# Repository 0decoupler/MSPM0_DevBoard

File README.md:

# MSPM0 MCU Devboard

some of the problems as of now:
- [ ] SPI, PWM, and GPIO header traces are trash, made the whole layout a spaghetti
- [ ] long via traces through the bottom layer, which is a rael problem
- [ ] some signal lines like PWM and ADC are subject to noise pickup due to closeness to 3V3 and VBUS thick traces.
- [ ] LDO's GND and VBUS copper fill field zones are killing my eyes. seems like abstract art or smth.
- [ ] ... 

3D View:

PCB Layout:

These are subject to change with each commit. Just to keep the repo neat.

⛄️

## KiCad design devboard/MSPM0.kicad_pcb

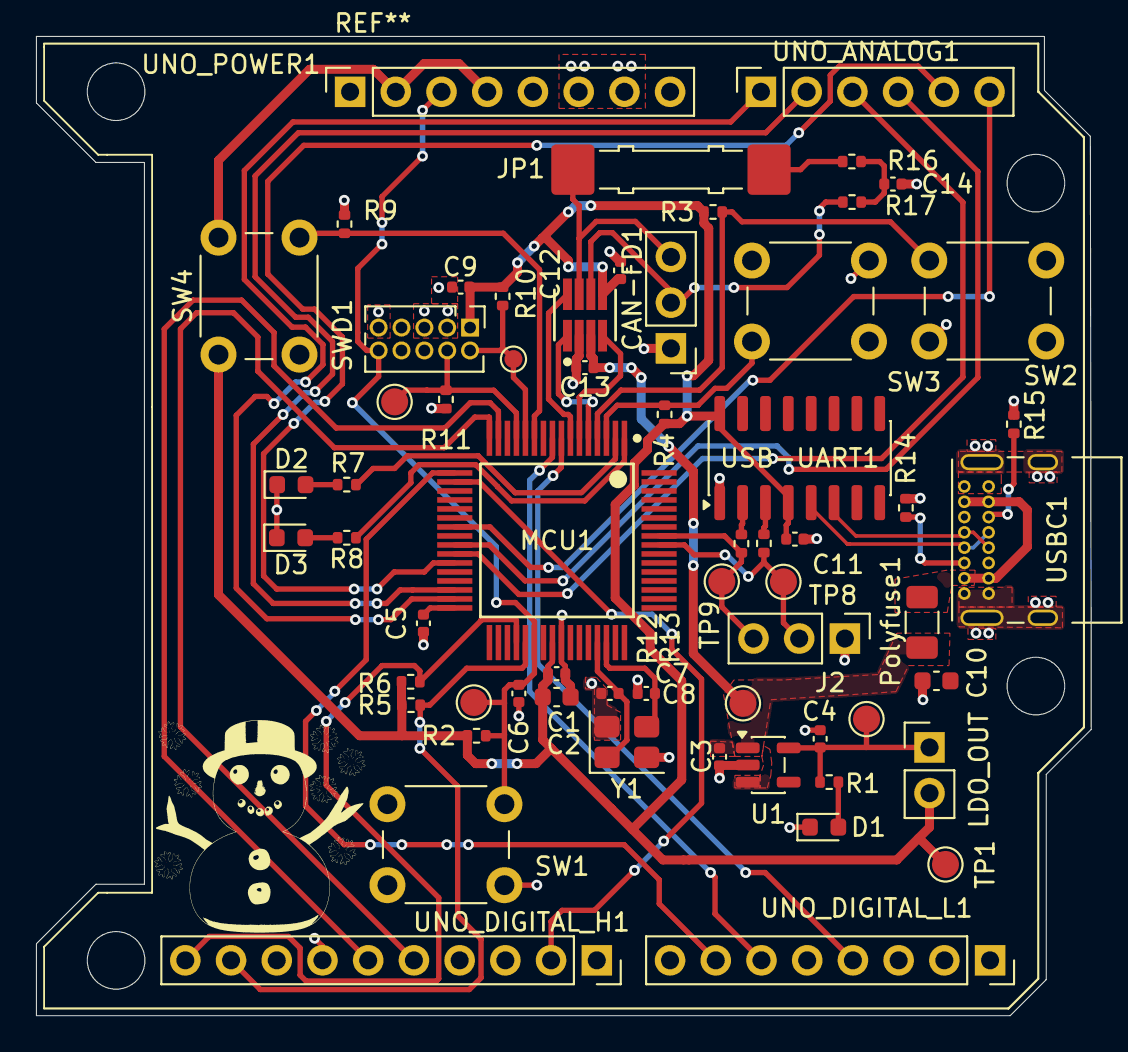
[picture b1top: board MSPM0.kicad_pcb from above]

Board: 2 copper layers, 58.6 x 54.4 mm, 62 parts (0 on the bottom side), 50 nets.

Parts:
C1, C10: 10u; C_0603_1608Metric
C2, C11, C12, C13: 100n; C_0402_1005Metric
C3, C4: 1u; C_0402_1005Metric
C5, C9: 470n; C_0402_1005Metric
C6: 10n; C_0402_1005Metric
C7, C8: 15p; C_0402_1005Metric
C14: 4n7; C_0402_1005Metric
CAN-FD1: TCAN1044AVDDFRQ1.A; DDF0008A-IPC_A
D1: RED; LED_0603_1608Metric
D2: BLUE; LED_0603_1608Metric
D3: GREEN; LED_0603_1608Metric
J2, J3: Conn_01x03_Pin; PinHeader_1x03_P2.54mm_Vertical
JP1: Jumper_2_Bridged; Jumper_Harwin_S1621_P10.9mm
LDO_OUT: Conn_01x02; PinHeader_1x02_P2.54mm_Vertical
MCU1: MSPM0G3507SPMR (LQFP-64); PM0064A-IPC_A
Polyfuse1: 500mA; Fuse_1206_3216Metric
R1: 470R; R_0402_1005Metric
R2, R9: 47k; R_0402_1005Metric
R3, R4, R10, R11: 10k; R_0402_1005Metric
R5, R6: 4k7; R_0402_1005Metric
R7, R8, R12, R13: 1k; R_0402_1005Metric
R14, R15: 5k1; R_0402_1005Metric
R16, R17: 62R; R_0402_1005Metric
SW1: SW_Push; SW_PUSH_6mm
SW2, SW3: SW_Push; SW_PUSH_6mm_H7.3mm
SW4: SW; SW_PUSH_6mm
SWD1: SWD; PinHeader_2x05_P1.27mm_Vertical
TP1, TP3: TP_3V3; TestPoint_Pad_D1.5mm
TP2: TP_5V; TestPoint_Pad_D1.5mm
TP5: TP_NRST; TestPoint_Pad_D1.5mm
TP6: TP_SWDIO; TestPoint_Pad_D1.0mm
TP7: TP_SWDCLK; TestPoint_Pad_D1.5mm
TP8: TP_UART_TX; TestPoint_Pad_D1.5mm
TP9: TP_UART_RX; TestPoint_Pad_D1.5mm
U1: AP2112K-3.3; SOT-23-5
UNO_ANALOG1: Conn_01x06_Analog; PinSocket_1x06_P2.54mm_Vertical
UNO_DIGITAL_H1: Conn_01x10_DigitalHigh; PinSocket_1x10_P2.54mm_Vertical
UNO_DIGITAL_L1: Conn_01x08_DigitalLow; PinSocket_1x08_P2.54mm_Vertical
UNO_POWER1: Conn_01x08_Power; PinSocket_1x08_P2.54mm_Vertical
USB-UART1: CH340C; SOIC-16_3.9x9.9mm_P1.27mm
USBC1: USB_C_Receptacle; USB_C_Receptacle_GCT_USB4085
Y1: 40MHz; Crystal_SMD_3225-4Pin_3.2x2.5mm

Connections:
+3V3: C1.1, C2.1, C9.1, C11.2, C12.1, CAN-FD1.5 (VIO), LDO_OUT.2, MCU1.40 (VDD), R2.1, R3.1, R4.1, R5.1, R6.1, R10.1, SW4.1, SWD1.1 (VTref), TP1.1 (1_1), UNO_POWER1.2, UNO_POWER1.4, USB-UART1.4 (V3), USB-UART1.16 (VCC)
/ADC12_0: MCU1.31 (PA27_A0_0_CAN_RX), UNO_ANALOG1.1
/ADC12_1: MCU1.30 (PA26_A0_1_CAN_TX), UNO_ANALOG1.2
/ADC12_2: MCU1.26 (PA25_A0_2), UNO_ANALOG1.3
/ADC12_3: MCU1.25 (PA24_A0_3), UNO_ANALOG1.4
/ADC12_4: MCU1.27 (PB25_A0_4), UNO_ANALOG1.5
/ADC12_5: MCU1.23 (PB24_A0_5), UNO_ANALOG1.6
/CANH: CAN-FD1.7 (CANH), J3.3, JP1.1 (A)
/CANL: CAN-FD1.6 (CANL), J3.2, R17.2
/CAN_RX: CAN-FD1.4 (RXD), MCU1.6 (PA13_CAN_RX)
/CAN_TX: CAN-FD1.1 (TXD), MCU1.5 (PA12_CAN_TX)
/GPIO_Button1: MCU1.3 (PB15), R4.2, SW3.1, UNO_DIGITAL_L1.3
/GPIO_Button2: MCU1.4 (PB16), R3.2, SW2.1, UNO_DIGITAL_L1.5
/GPIO_CAN_STB: CAN-FD1.8 (STB), MCU1.7 (PA14)
/GPIO_LED1: MCU1.1 (PB13), R8.1, UNO_DIGITAL_L1.8
/GPIO_LED2: MCU1.2 (PB14), R7.1, UNO_DIGITAL_H1.1
/I2C_SCL: MCU1.36 (PA29), R6.2, UNO_DIGITAL_H1.10
/I2C_SDA: MCU1.37 (PA30), R5.2, UNO_DIGITAL_H1.9
/NRST: C6.1, MCU1.38 (RST_N), R2.2, SW1.2, SWD1.10 (~RESET), TP5.1 (1_1), UNO_POWER1.3
/PWM0_CCP0: MCU1.8 (PA15_A1_0), UNO_DIGITAL_L1.4
/PWM0_CCP1: MCU1.9 (PA16_A1_1), UNO_DIGITAL_L1.6
/PWM1_CCP0: MCU1.17 (PA21_A1_7_VREF-), UNO_DIGITAL_L1.7
/PWM1_CCP1: MCU1.18 (PA22_A0_7), UNO_DIGITAL_H1.2
/PWR_LED0_K: D1.2 (A), R1.1
/PWR_LED1_K: D3.2 (A), R8.2
/PWR_LED2_K: D2.2 (A), R7.2
/SPI_CS0: MCU1.54 (PA8), UNO_DIGITAL_H1.3
/SPI_PICO: MCU1.55 (PA9), UNO_DIGITAL_H1.4
/SPI_POCI: MCU1.16 (PB19_A1_6), UNO_DIGITAL_H1.5
/SPI_SCLK: MCU1.15 (PB18_A1_5), UNO_DIGITAL_H1.6
/SWCLK: MCU1.13 (PA20_SWCLK), R11.1, SWD1.4 (SWCLK/TCK), TP7.1 (1_1)
/SWDIO: MCU1.12 (PA19_SWDIO), R10.2, SWD1.2 (SWDIO/TMS), TP6.1 (1_1)
/UART0_RX: J2.3, MCU1.57 (PA11), R12.2, TP9.1 (1_1), UNO_DIGITAL_L1.1
/UART0_TX: J2.2, MCU1.56 (PA10), R13.2, TP8.1 (1_1), UNO_DIGITAL_L1.2
/USB_D+: USB-UART1.5 (UD+), USBC1.A6 (D+), USBC1.B6 (D+)
/USB_D-: USB-UART1.6 (UD-), USBC1.A7 (D-), USBC1.B7 (D-)
/VCORE: C5.1, MCU1.32 (VCORE)
/XIN: C7.1, MCU1.45 (PA5_HFXIN), Y1.1
/XOUT: C8.1, MCU1.46 (PA6_HFXOUT), Y1.3
GND: C1.2, C2.2, C3.2, C4.2, C5.2, C6.2, C7.2, C8.2, C9.2, C10.1, C11.1, C12.2, C13.2, C14.2, CAN-FD1.2 (GND), D1.1 (K), D2.1 (K), D3.1 (K), J2.1, J3.1, MCU1.41 (VSS), R9.2, R11.2, R14.1, R15.1, SW1.1, SW2.2, SW3.2, SWD1.3 (GND), SWD1.5 (GND), SWD1.9 (GNDDetect), U1.2 (GND), UNO_DIGITAL_H1.7, UNO_POWER1.6, UNO_POWER1.7, USB-UART1.1 (GND), USBC1.A1 (GND), USBC1.A12 (GND), USBC1.B1 (GND), USBC1.B12 (GND), USBC1.SH (SHIELD), Y1.2 (G), Y1.4 (G)
unnamed: C14.1, R16.2, R17.1
unnamed: C4.1, LDO_OUT.1, R1.2, TP3.1 (1_1), U1.5 (VOUT)
unnamed: JP1.2 (B), R16.1
unnamed: MCU1.11 (PA18_A1_3), R9.1, SW4.2
unnamed: Polyfuse1.2, USBC1.A4 (VBUS), USBC1.A9 (VBUS), USBC1.B4 (VBUS), USBC1.B9 (VBUS)
unnamed: R13.1, USB-UART1.3 (RXD)
unnamed: R12.1, USB-UART1.2 (TXD)
unnamed: R14.2, USBC1.A5 (CC1)
unnamed: R15.2, USBC1.B5 (CC2)
VBUS: C3.1, C10.2, C13.1, CAN-FD1.3 (VCC), Polyfuse1.1, TP2.1 (1_1), U1.1 (VIN), U1.3 (EN), UNO_POWER1.5
